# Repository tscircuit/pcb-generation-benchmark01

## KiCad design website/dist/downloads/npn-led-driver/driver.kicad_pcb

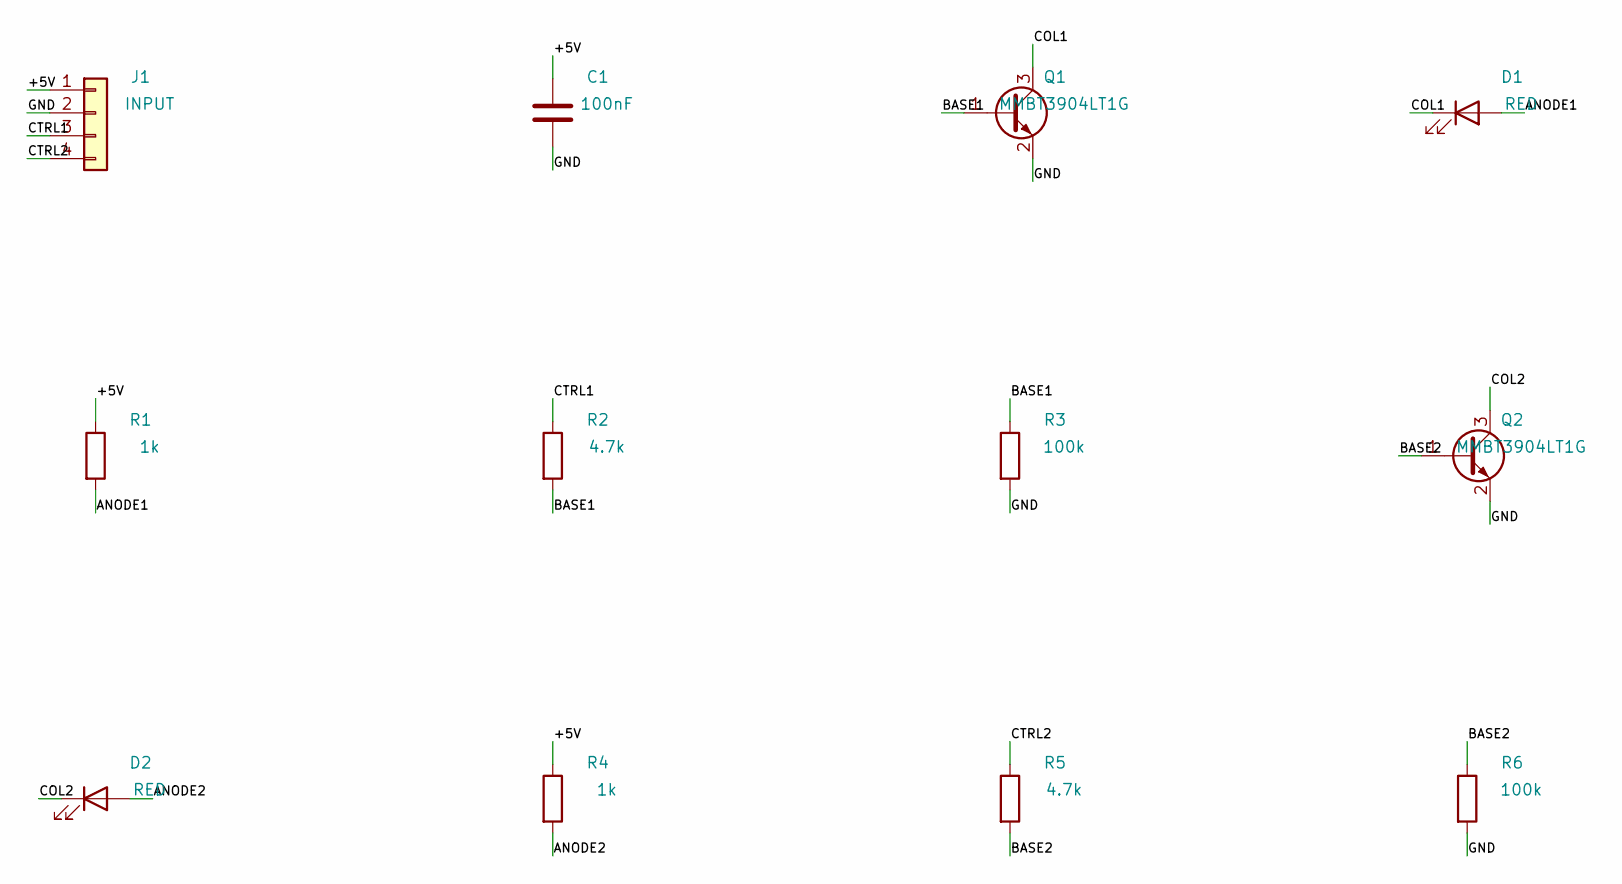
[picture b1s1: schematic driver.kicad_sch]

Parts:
C1: 100nF; C_0805_2012Metric
D1, D2: RED; LED_0805_2012Metric
J1: INPUT; PinHeader_1x04_P2.54mm_Vertical
Q1, Q2: MMBT3904LT1G; SOT-23
R1, R4: 1k; R_0805_2012Metric
R2, R5: 4.7k; R_0805_2012Metric
R3, R6: 100k; R_0805_2012Metric

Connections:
+5V: C1.1, J1.1, R1.1, R4.1
ANODE1: D1.2 (A), R1.2
ANODE2: D2.2 (A), R4.2
BASE1: Q1.1 (B), R2.2, R3.1
BASE2: Q2.1 (B), R5.2, R6.1
COL1: D1.1 (K), Q1.3 (C)
COL2: D2.1 (K), Q2.3 (C)
CTRL1: J1.3, R2.1
CTRL2: J1.4, R5.1
GND: C1.2, J1.2, Q1.2 (E), Q2.2 (E), R3.2, R6.2

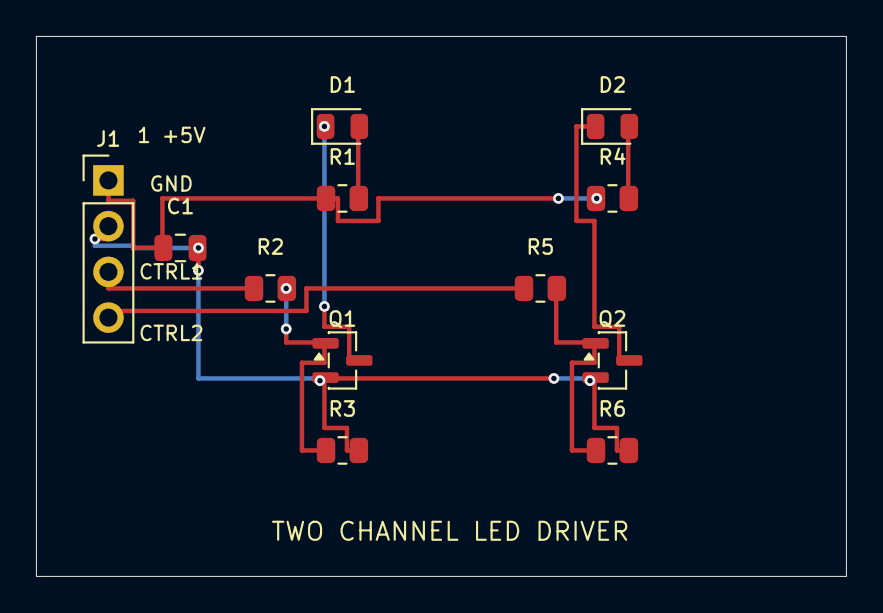
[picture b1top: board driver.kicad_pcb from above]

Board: 2 copper layers, 45.0 x 30.0 mm, 12 parts (0 on the bottom side), 10 nets.

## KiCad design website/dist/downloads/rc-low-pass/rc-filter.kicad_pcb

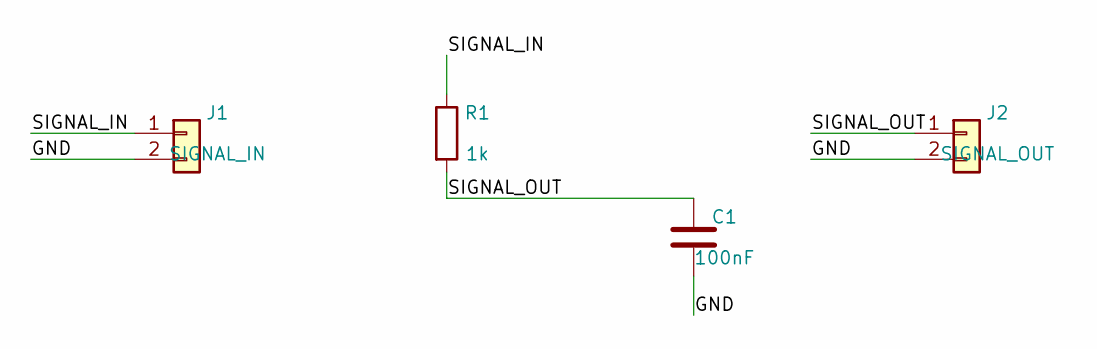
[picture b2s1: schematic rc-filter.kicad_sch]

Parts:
C1: 100nF; C_0805_2012Metric
J1: SIGNAL_IN; PinHeader_1x02_P2.54mm_Vertical
J2: SIGNAL_OUT; PinHeader_1x02_P2.54mm_Vertical
R1: 1k; R_0805_2012Metric

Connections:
/GND: C1.2, J1.2, J2.2
/SIGNAL_IN: J1.1, R1.1
/SIGNAL_OUT: C1.1, J2.1, R1.2

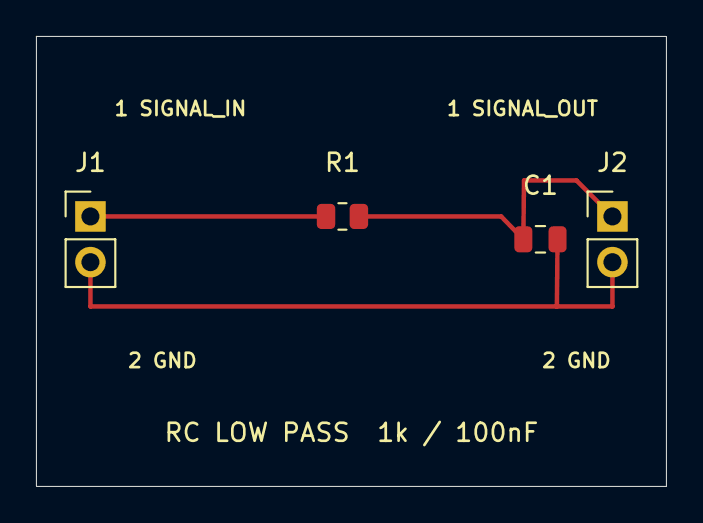
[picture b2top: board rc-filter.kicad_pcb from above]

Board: 2 copper layers, 35.0 x 25.0 mm, 4 parts (0 on the bottom side), 3 nets.
